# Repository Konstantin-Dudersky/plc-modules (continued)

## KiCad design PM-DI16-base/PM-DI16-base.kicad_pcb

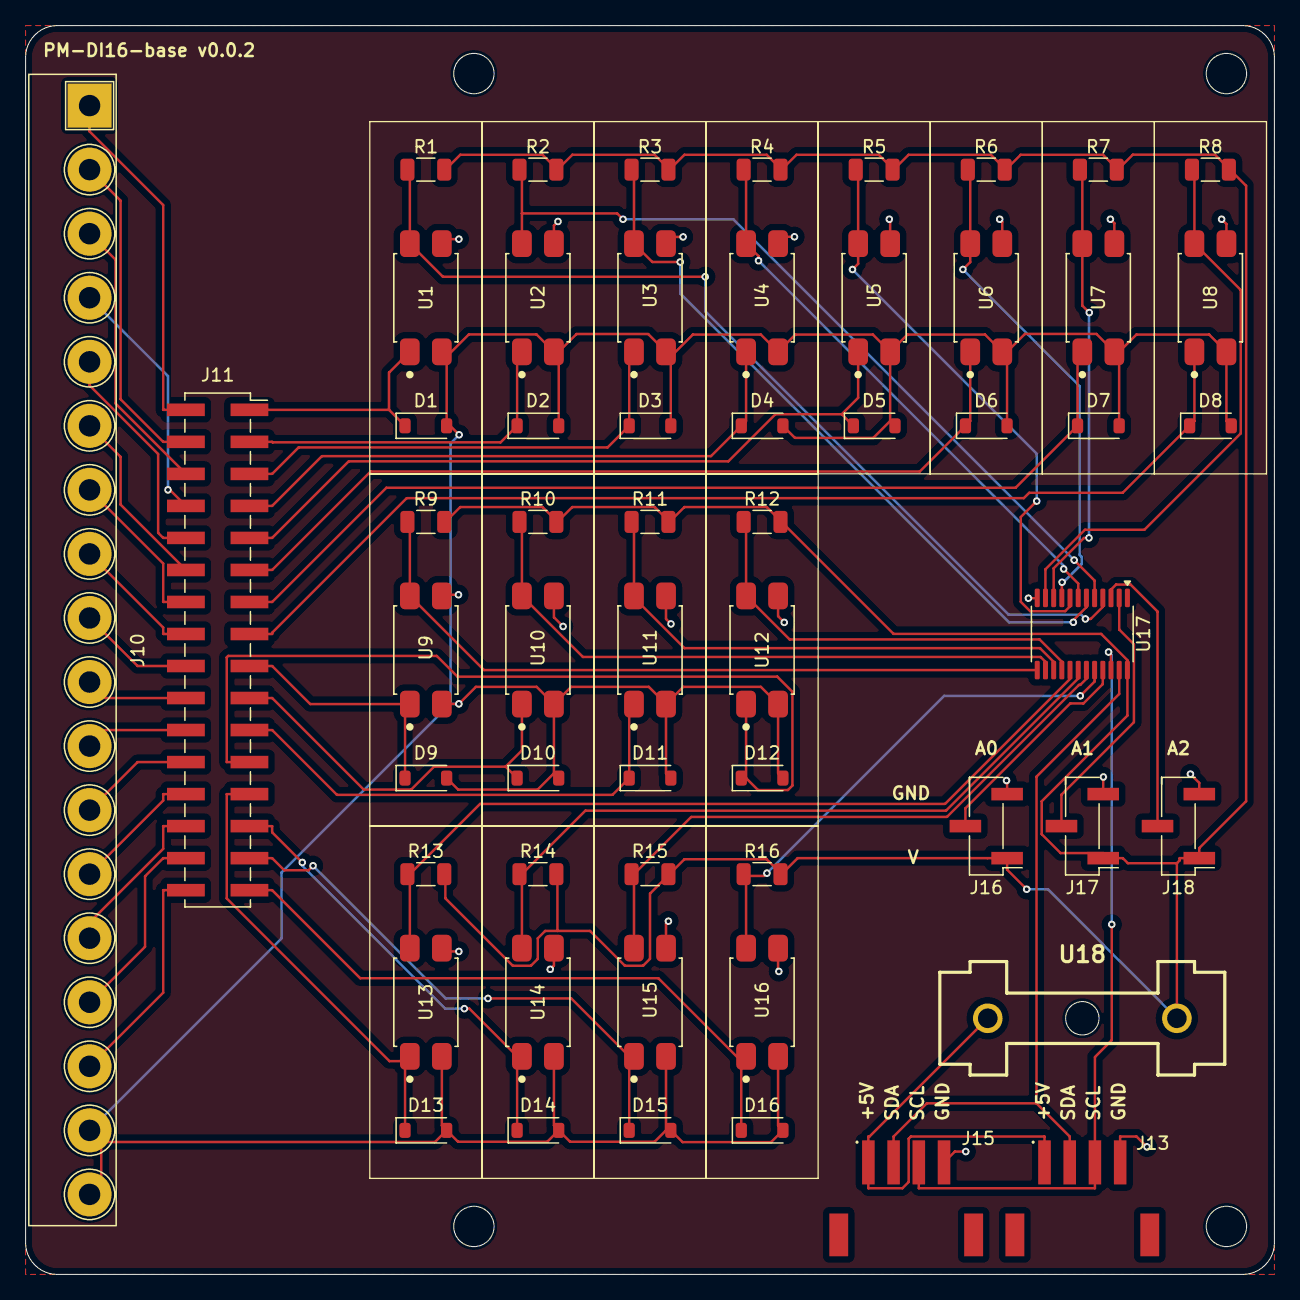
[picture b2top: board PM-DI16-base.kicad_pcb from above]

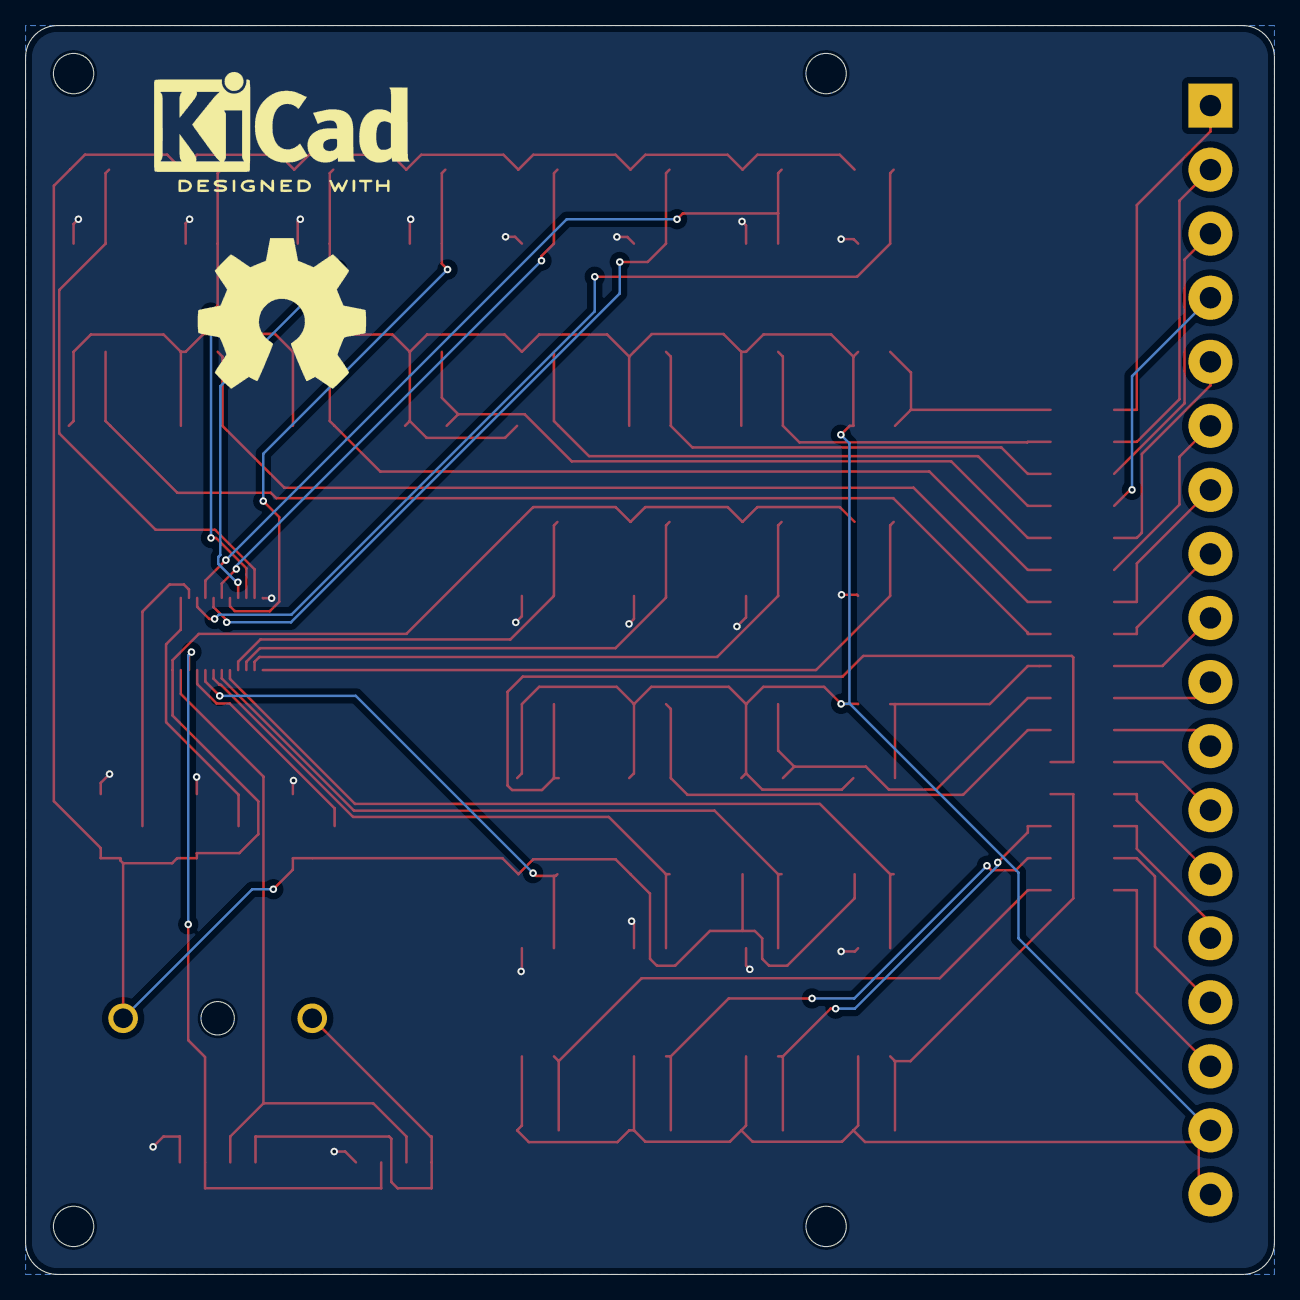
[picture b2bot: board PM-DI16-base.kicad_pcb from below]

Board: 2 copper layers, 99.1 x 99.1 mm, 63 parts (2 on the bottom side), 57 nets.

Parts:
D1, D2, D3, D4, D5, D6, D7, D8, D9, D10, D11, D12, D13, D14, D15, D16: 1N4148W; D_SOD-123
H1, H2, H3, H4: MountingHole; MountingHole_3.2mm_M3
J10: 2EDGR-5.08-18P; Degson_2EDGR-5.08-18P
J11: Conn_02x16_socket
J13, J15: S4B-PH-SM4-TB; JST_S4B-PH-SM4-TB_JST_S4B-PH-SM4-TB
J16, J17, J18: Conn_01x03; PinHeader_1x03_P2.54mm_Vertical_SMD_Pin1Left
R1, R2, R3, R4, R5, R6, R7, R8, R9, R10, R11, R12, R13, R14, R15, R16: 10k 0.25W; R_1206_3216Metric
U1, U2, U3, U4, U5, U6, U7, U8, U9, U10, U11, U12, U13, U14, U15, U16: PC817; PC817XI_SOIC254P975X460-4N
U17: PCA9555PW; TSSOP-24_4.4x7.8mm_P0.65mm
U18: 64900001039; Fuseholder
logo_kicad: KiCad-Logo2_8mm_SilkScreen
logo_oshw: OSHW-Symbol_13.4x12mm_SilkScreen

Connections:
/A0: J16.2, U17.21 (A0)
/A1: J17.2, U17.2 (A1)
/A2: J18.2, U17.3 (A2)
/M: D1.2 (A), D2.2 (A), D3.2 (A), D4.2 (A), D5.2 (A), D6.2 (A), D7.2 (A), D8.2 (A), D9.2 (A), D10.2 (A), D11.2 (A), D12.2 (A), D13.2 (A), D14.2 (A), D15.2 (A), D16.2 (A), J10.17, J10.18, U1.2, U2.2, U3.2, U4.2, U5.2, U6.2, U7.2, U8.2, U9.2, U10.2, U11.2, U12.2, U13.2, U14.2, U15.2, U16.2
/SCL: J13.3, J15.3, U17.22 (SCL)
/SDA: J13.2, J15.2, U17.23 (SDA)
GND: J13.4, J15.4, J16.3, J17.3, J18.3, U1.3, U2.3, U3.3, U4.3, U5.3, U6.3, U7.3, U8.3, U9.3, U10.3, U11.3, U12.3, U13.3, U14.3, U15.3, U16.3, U17.12 (VSS)
unnamed: D1.1 (K), J11.1, U1.1
unnamed: D2.1 (K), J11.3, U2.1
unnamed: D3.1 (K), J11.5, U3.1
unnamed: D4.1 (K), J11.7, U4.1
unnamed: D5.1 (K), J11.9, U5.1
unnamed: D6.1 (K), J11.11, U6.1
unnamed: D7.1 (K), J11.13, U7.1
unnamed: D8.1 (K), J11.15, U8.1
unnamed: D9.1 (K), J11.17, U9.1
unnamed: D10.1 (K), J11.19, U10.1
unnamed: D11.1 (K), J11.21, U11.1
unnamed: D12.1 (K), J11.23, U12.1
unnamed: D13.1 (K), J11.25, U13.1
unnamed: D14.1 (K), J11.27, U14.1
unnamed: D15.1 (K), J11.29, U15.1
unnamed: D16.1 (K), J11.31, U16.1
unnamed: J10.1, J11.2
unnamed: J10.2, J11.4
unnamed: J10.3, J11.6
unnamed: J10.4, J11.8
unnamed: J10.5, J11.10
unnamed: J10.6, J11.12
unnamed: J10.7, J11.14
unnamed: J10.8, J11.16
unnamed: J10.9, J11.18
unnamed: J10.10, J11.20
unnamed: J10.11, J11.22
unnamed: J10.12, J11.24
unnamed: J10.13, J11.26
unnamed: J10.14, J11.28
unnamed: J10.15, J11.30
unnamed: J10.16, J11.32
unnamed: J13.1, J15.1, U18.2
unnamed: R1.1, U1.4, U17.4 (IO0_0)
unnamed: R2.1, U2.4, U17.5 (IO0_1)
unnamed: R3.1, U3.4, U17.6 (IO0_2)
unnamed: R4.1, U4.4, U17.7 (IO0_3)
unnamed: R5.1, U5.4, U17.8 (IO0_4)
unnamed: R6.1, U6.4, U17.9 (IO0_5)
unnamed: R7.1, U7.4, U17.10 (IO0_6)
unnamed: R8.1, U8.4, U17.11 (IO0_7)
unnamed: R9.1, U9.4, U17.13 (IO1_0)
unnamed: R10.1, U10.4, U17.14 (IO1_1)
unnamed: R11.1, U11.4, U17.15 (IO1_2)
unnamed: R12.1, U12.4, U17.16 (IO1_3)
unnamed: R13.1, U13.4, U17.17 (IO1_4)
unnamed: R14.1, U14.4, U17.18 (IO1_5)
unnamed: R15.1, U15.4, U17.19 (IO1_6)
unnamed: R16.1, U16.4, U17.20 (IO1_7)
VDD: J16.1, J17.1, J18.1, R1.2, R2.2, R3.2, R4.2, R5.2, R6.2, R7.2, R8.2, R9.2, R10.2, R11.2, R12.2, R13.2, R14.2, R15.2, R16.2, U17.24 (VDD), U18.1

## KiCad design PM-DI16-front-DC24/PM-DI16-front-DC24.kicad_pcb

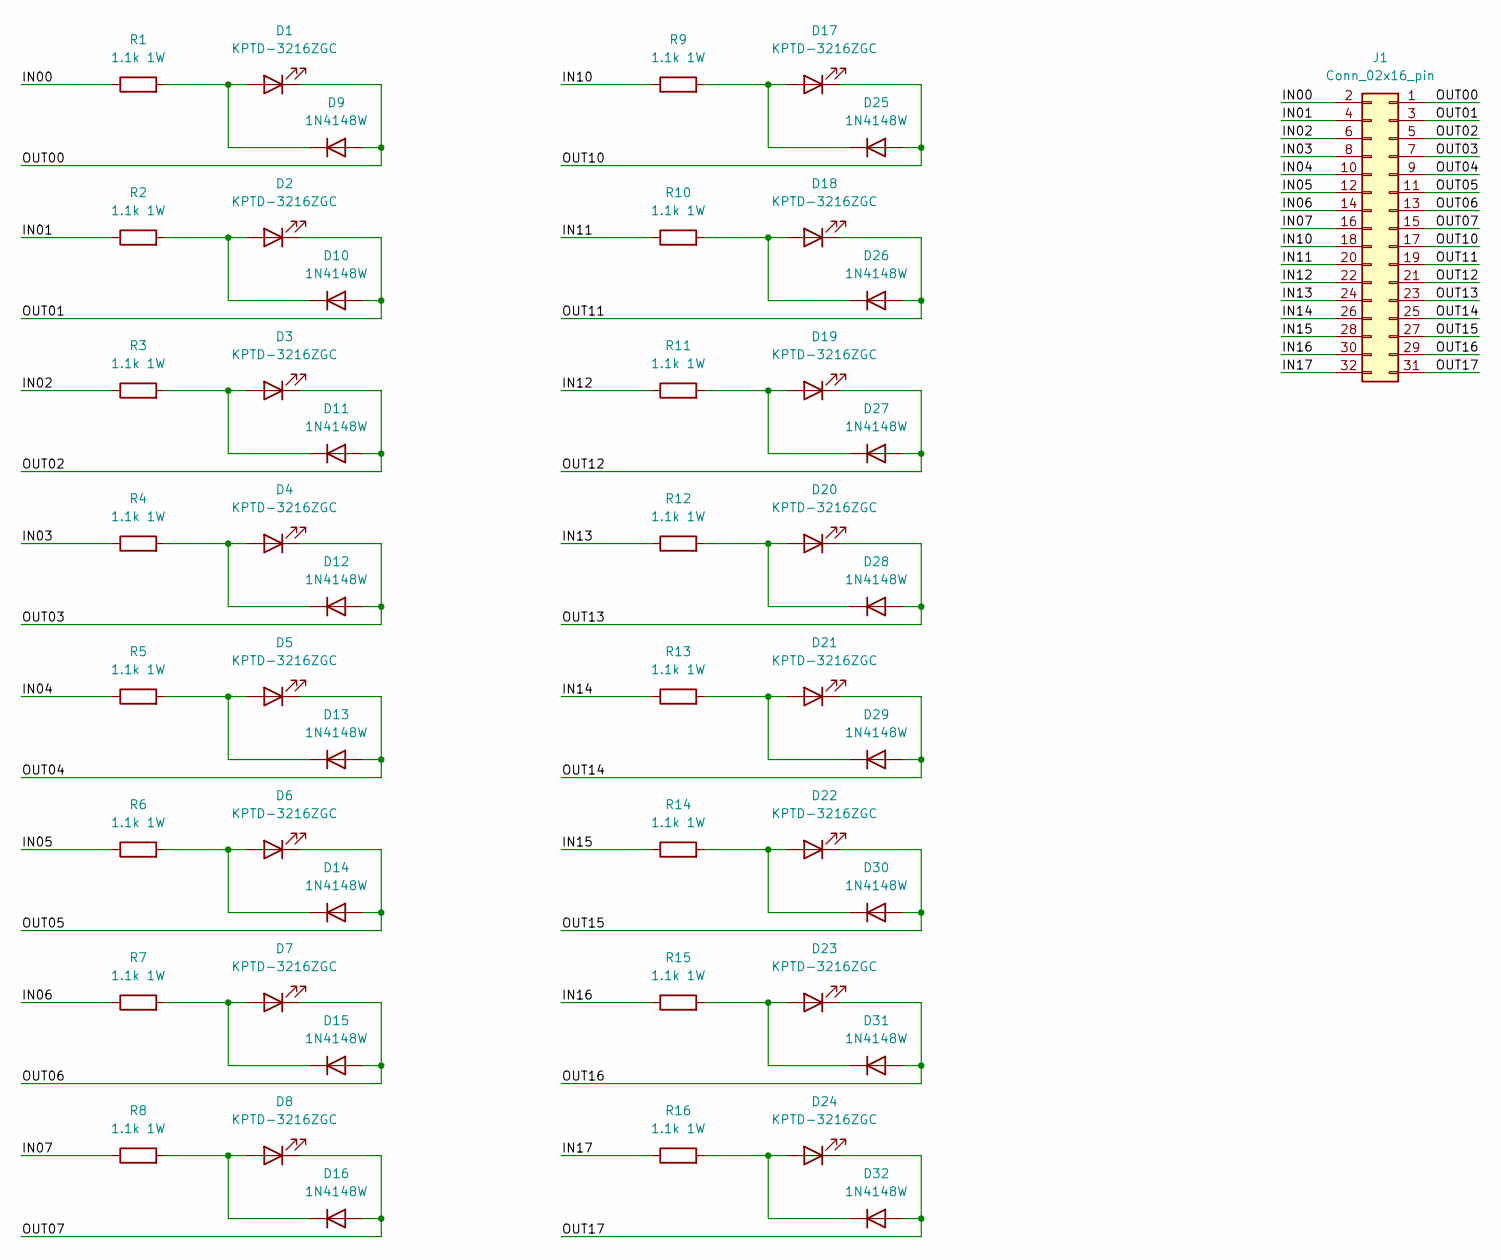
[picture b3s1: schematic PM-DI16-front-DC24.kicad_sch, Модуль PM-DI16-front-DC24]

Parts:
D1, D2, D3, D4, D5, D6, D7, D8, D17, D18, D19, D20, D21, D22, D23, D24: KPTD-3216ZGC; LED_KPTD-3216ZGC
D9, D10, D11, D12, D13, D14, D15, D16, D25, D26, D27, D28, D29, D30, D31, D32: 1N4148W; D_SOD-123; MfrPart 1N4148W
J1: Conn_02x16_pin
R1, R2, R3, R4, R5, R6, R7, R8, R9, R10, R11, R12, R13, R14, R15, R16: 1.1k 1W; R_2512_6332Metric_Pad1.40x3.35mm_HandSolder; MfgPart FRC2512F1101TS

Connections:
/IN00: J1.2, R1.1
/IN01: J1.4, R2.1
/IN02: J1.6, R3.1
/IN03: J1.8, R4.1
/IN04: J1.10, R5.1
/IN05: J1.12, R6.1
/IN06: J1.14, R7.1
/IN07: J1.16, R8.1
/IN10: J1.18, R9.1
/IN11: J1.20, R10.1
/IN12: J1.22, R11.1
/IN13: J1.24, R12.1
/IN14: J1.26, R13.1
/IN15: J1.28, R14.1
/IN16: J1.30, R15.1
/IN17: J1.32, R16.1
/OUT00: D1.1 (K), D9.2 (A), J1.1
/OUT01: D2.1 (K), D10.2 (A), J1.3
/OUT02: D3.1 (K), D11.2 (A), J1.5
/OUT03: D4.1 (K), D12.2 (A), J1.7
/OUT04: D5.1 (K), D13.2 (A), J1.9
/OUT05: D6.1 (K), D14.2 (A), J1.11
/OUT06: D7.1 (K), D15.2 (A), J1.13
/OUT07: D8.1 (K), D16.2 (A), J1.15
/OUT10: D17.1 (K), D25.2 (A), J1.17
/OUT11: D18.1 (K), D26.2 (A), J1.19
/OUT12: D19.1 (K), D27.2 (A), J1.21
/OUT13: D20.1 (K), D28.2 (A), J1.23
/OUT14: D21.1 (K), D29.2 (A), J1.25
/OUT15: D22.1 (K), D30.2 (A), J1.27
/OUT16: D23.1 (K), D31.2 (A), J1.29
/OUT17: D24.1 (K), D32.2 (A), J1.31
unnamed: D1.2 (A), D9.1 (K), R1.2
unnamed: D2.2 (A), D10.1 (K), R2.2
unnamed: D3.2 (A), D11.1 (K), R3.2
unnamed: D4.2 (A), D12.1 (K), R4.2
unnamed: D5.2 (A), D13.1 (K), R5.2
unnamed: D6.2 (A), D14.1 (K), R6.2
unnamed: D7.2 (A), D15.1 (K), R7.2
unnamed: D8.2 (A), D16.1 (K), R8.2
unnamed: D17.2 (A), D25.1 (K), R9.2
unnamed: D18.2 (A), D26.1 (K), R10.2
unnamed: D19.2 (A), D27.1 (K), R11.2
unnamed: D20.2 (A), D28.1 (K), R12.2
unnamed: D21.2 (A), D29.1 (K), R13.2
unnamed: D22.2 (A), D30.1 (K), R14.2
unnamed: D23.2 (A), D31.1 (K), R15.2
unnamed: D24.2 (A), D32.1 (K), R16.2

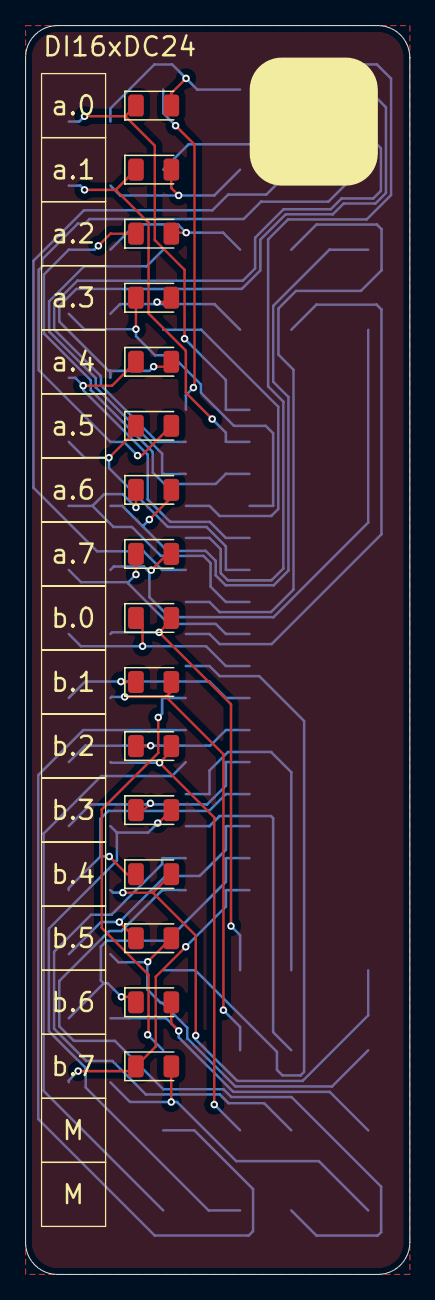
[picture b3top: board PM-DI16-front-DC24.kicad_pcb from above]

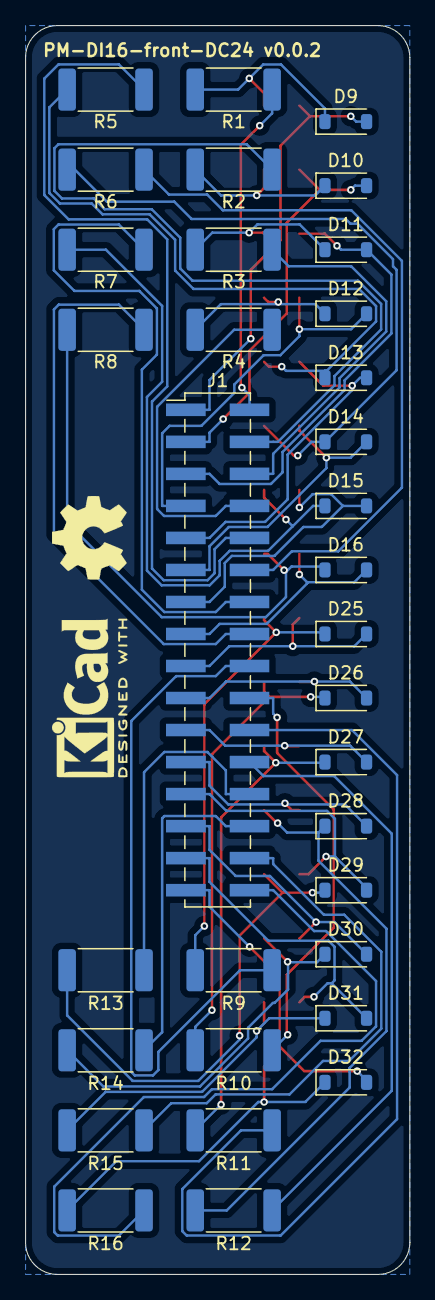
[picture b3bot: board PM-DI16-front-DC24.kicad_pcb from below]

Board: 2 copper layers, 30.5 x 99.1 mm, 50 parts (34 on the bottom side), 48 nets.

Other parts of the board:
Logo_kicad: KiCad-Logo2_5mm_SilkScreen

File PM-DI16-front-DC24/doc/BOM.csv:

"Reference","Value","Qty","NextPCB_price","NextPCB_url","Datasheet"
"D1,D2,D3,D4,D5,D6,D7,D8,D17,D18,D19,D20,D21,D22,D23,D24","KPTD-3216ZGC ","16","0.39735","https://www.hqonline.com/product-detail/kingbright-kptd-3216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","https://www.kingbright.com/content/listitem/psearch/170"
"D9,D10,D11,D12,D13,D14,D15,D16,D25,D26,D27,D28,D29,D30,D31,D32","1N4148W","16","0.00811","https://www.hqonline.com/product-detail/switching-diodes--sm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","~"
"J1,J2","Conn_02x08_Odd_Even","2","0.27407","https://www.hqonline.com/product-detail/pin-headers-hctl-pz2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","~"
"R1,R2,R3,R4,R5,R6,R7,R8,R9,R10,R11,R12,R13,R14,R15,R16","1.1k 1W","16","0.01655","https://www.hqonline.com/product-detail/chip-resistors-fojan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","https://www.hqonline.com/product-detail/chip-resistors-fojan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"

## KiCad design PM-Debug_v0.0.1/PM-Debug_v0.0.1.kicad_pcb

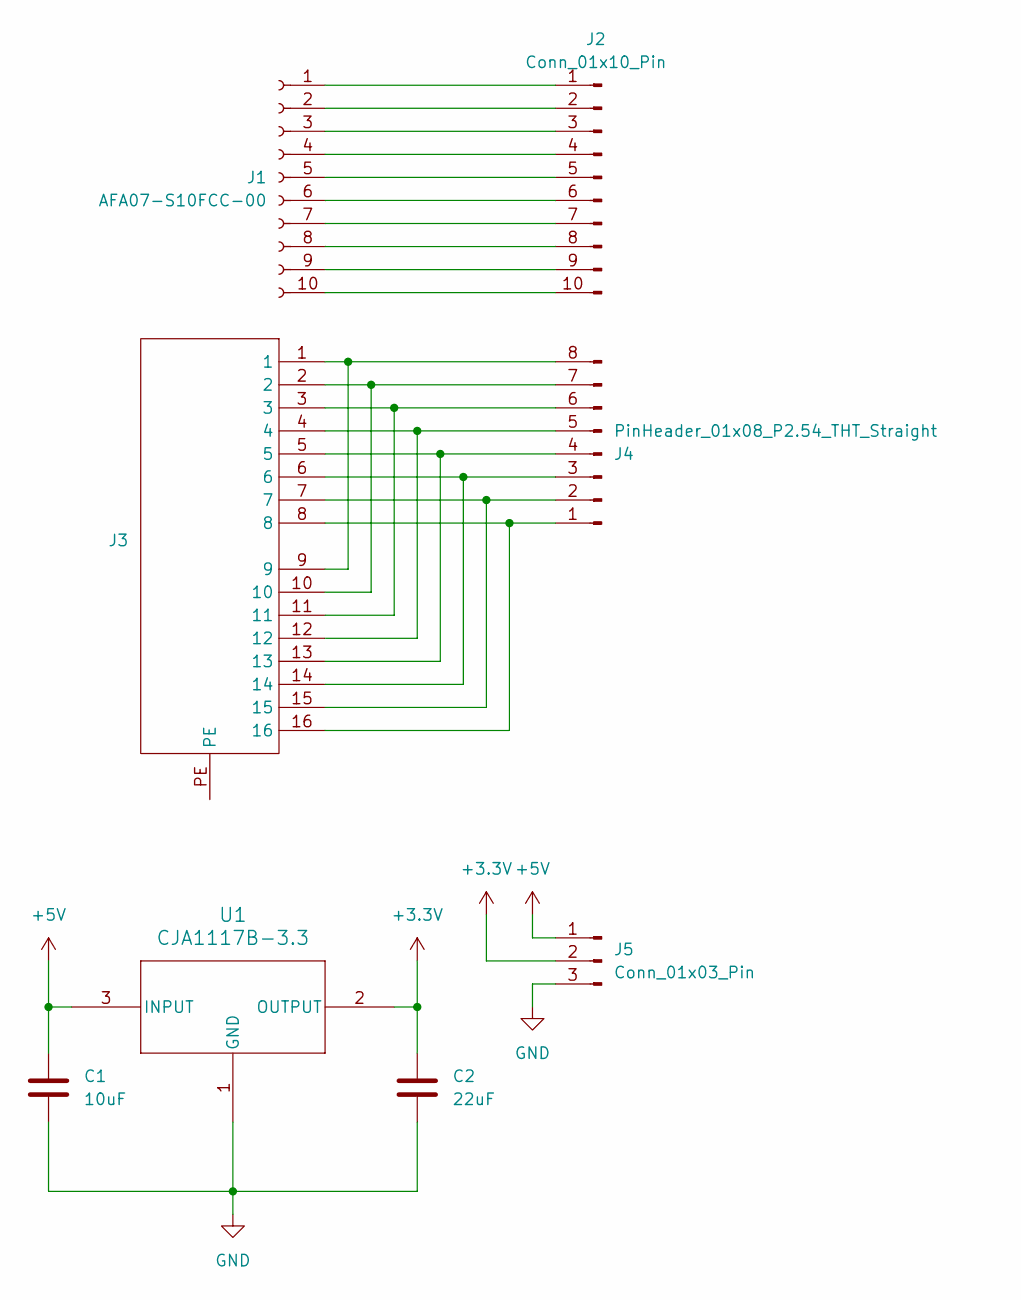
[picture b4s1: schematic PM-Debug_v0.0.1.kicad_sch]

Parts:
C1: 10uF; C_1206_3216Metric_Pad1.33x1.80mm_HandSolder; part_ipn C_10uF_16V_1206
C2: 22uF; C_1206_3216Metric_Pad1.33x1.80mm_HandSolder; part_ipn C_22uF_16V_1206
J1: AFA07-S10FCC-00; CONN10_AFA07-S10_JUS
J2: Conn_01x10_Pin; PinHeader_1x10_P2.54mm_Vertical
J3: HC-WK88-H16-1X2-DB
J4: PinHeader_01x08_P2.54_THT_Straight; PinHeader_1x08_P2.54mm_Vertical; part_ipn PinHeader_01x08_P2.54_THT_Straight
J5: Conn_01x03_Pin; PinHeader_1x03_P2.54mm_Vertical
U1: CJA1117B-3.3; SOT-89-3; part_ipn CJA1117B-3.3

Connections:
+3.3V: C2.1, J5.2, U1.2 (OUTPUT)
+5V: C1.1, J5.1, U1.3 (INPUT)
GND: C1.2, C2.2, J5.3, U1.1 (GND)
unnamed: J1.1, J2.1
unnamed: J1.2, J2.2
unnamed: J1.3, J2.3
unnamed: J1.4, J2.4
unnamed: J1.5, J2.5
unnamed: J1.6, J2.6
unnamed: J1.7, J2.7
unnamed: J1.8, J2.8
unnamed: J1.9, J2.9
unnamed: J1.10, J2.10
unnamed: J3.8, J3.16, J4.1
unnamed: J3.7, J3.15, J4.2
unnamed: J3.6, J3.14, J4.3
unnamed: J3.5, J3.13, J4.4
unnamed: J3.4, J3.12, J4.5
unnamed: J3.3, J3.11, J4.6
unnamed: J3.2, J3.10, J4.7
unnamed: J3.1, J3.9, J4.8

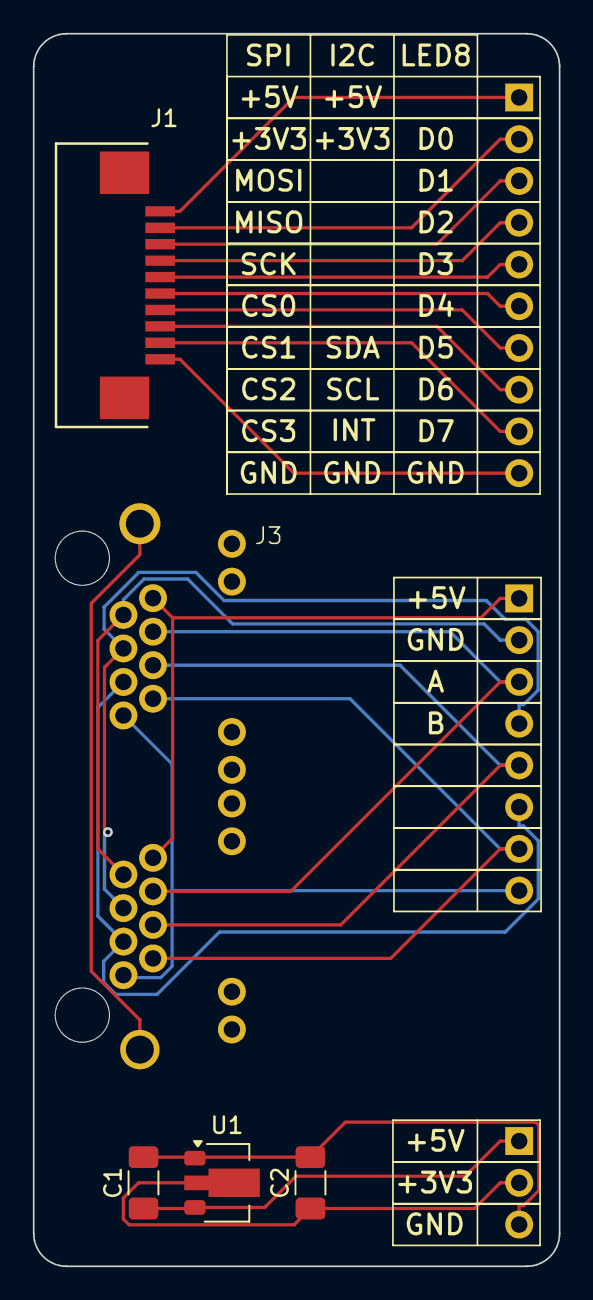
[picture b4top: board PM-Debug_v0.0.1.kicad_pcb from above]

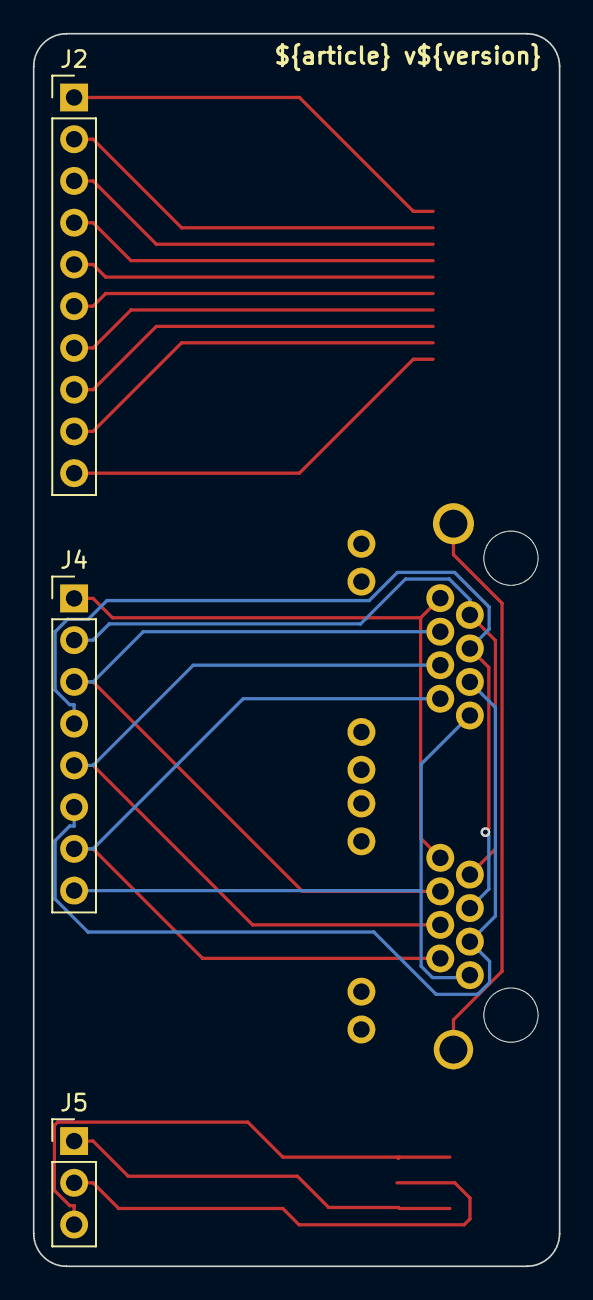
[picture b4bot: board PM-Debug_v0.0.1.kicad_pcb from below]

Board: 2 copper layers, 32.0 x 75.0 mm, 8 parts (3 on the bottom side), 21 nets.

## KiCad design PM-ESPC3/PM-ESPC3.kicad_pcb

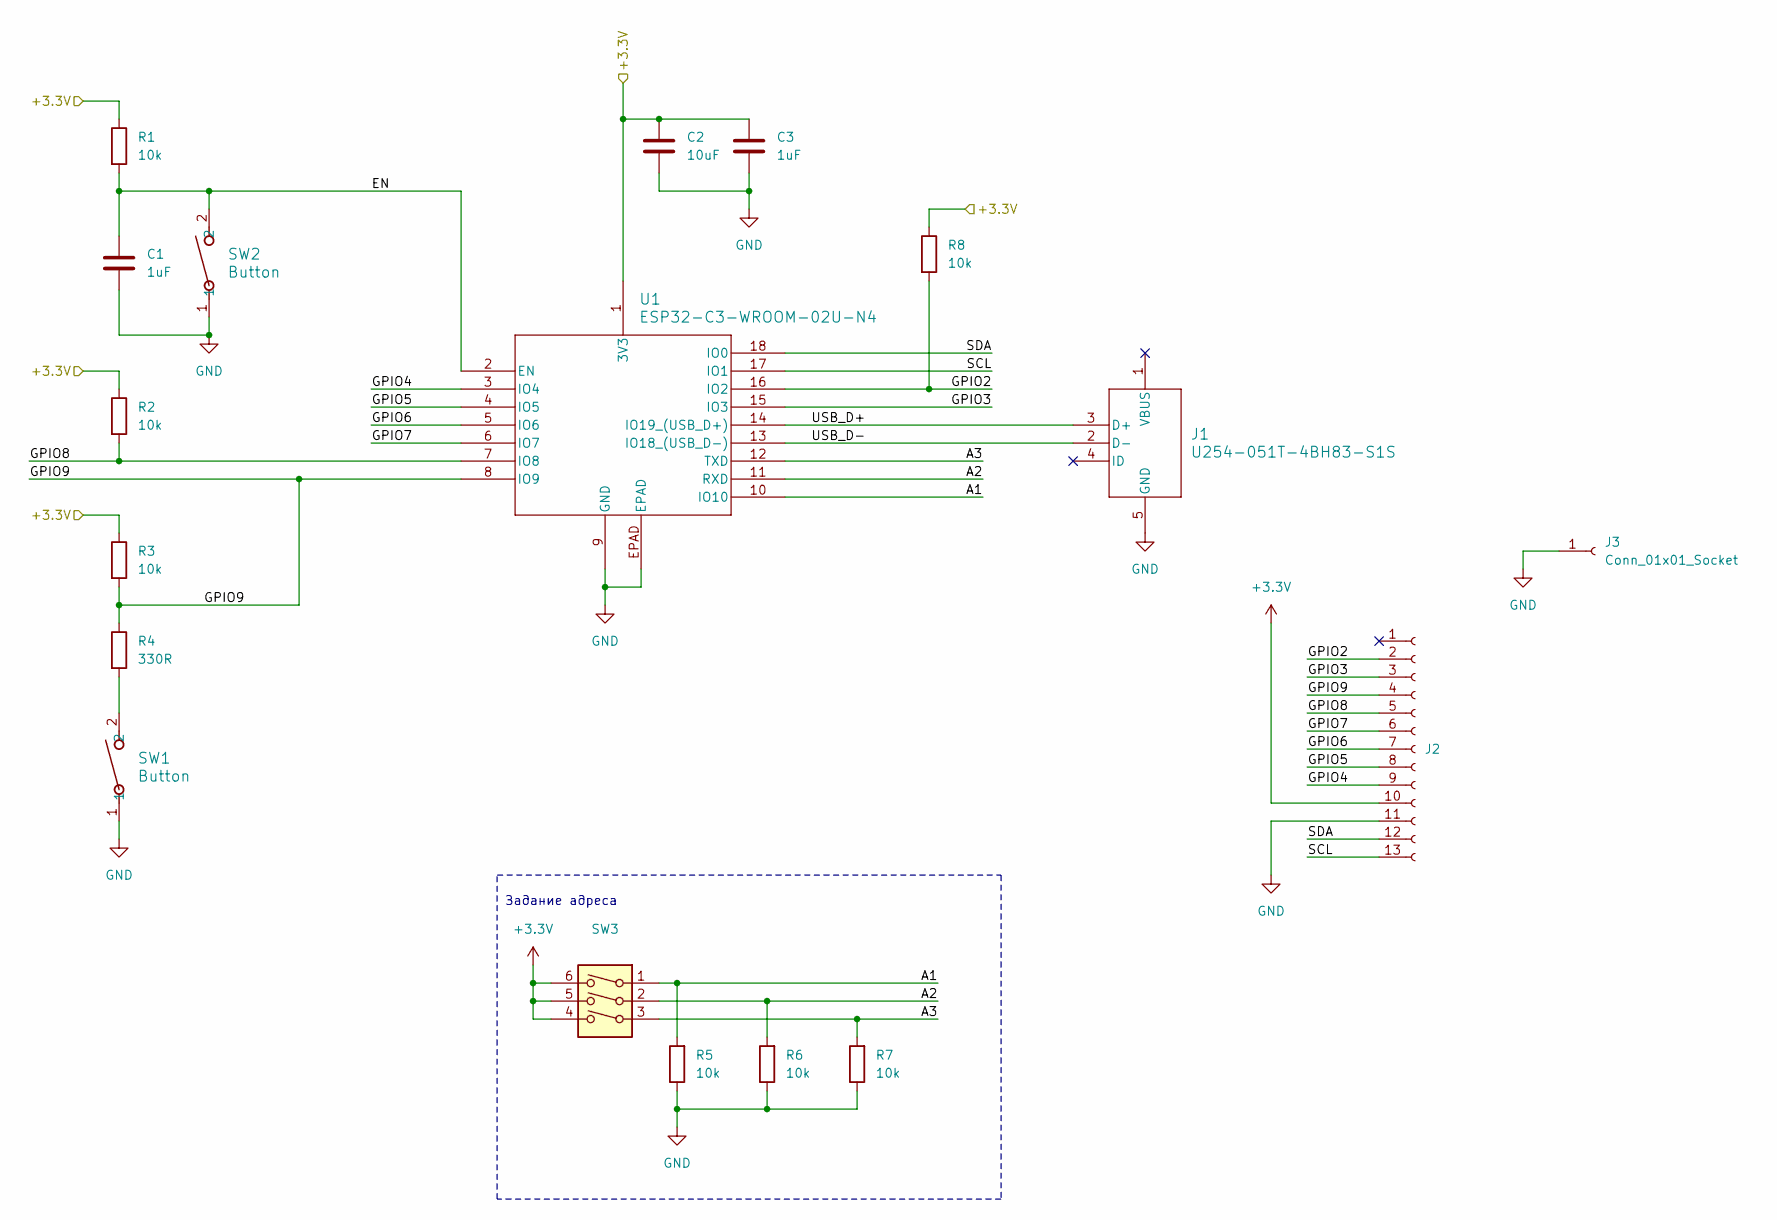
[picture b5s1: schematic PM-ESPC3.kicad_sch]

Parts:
C1: 1uF; C_1206_3216Metric_Pad1.33x1.80mm_HandSolder; part_ipn C_1uF_50V_1206
C2: 10uF; C_1206_3216Metric_Pad1.33x1.80mm_HandSolder; part_ipn C_10uF_16V_1206
C3: 1uF; C_1206_3216Metric_Pad1.33x1.80mm_HandSolder; part_ipn C_1uF_16V_1206
J1: U254-051T-4BH83-S1S; CONN5_H83-S1S_XKB; part_ipn U254-051T-4BH83-S1S
J2: Conn_01x13_Socket; PinHeader_1x13_P2.54mm_Vertical
J3: Conn_01x01_Socket; PinHeader_1x01_P2.54mm_Vertical
R1, R2, R3, R5, R6, R7, R8: 10k; R_1206_3216Metric_Pad1.30x1.75mm_HandSolder; part_ipn R_10k_1206_1%
R4: 330R; R_1206_3216Metric_Pad1.30x1.75mm_HandSolder; part_ipn R_330R_1206_1%
SW1, SW2: Button; SW_TS-1088_XNP-M; part_ipn TS-1088-AR02016
SW3: DIP_SW-3P-P2.54-THT-Top; SW_DIP_SPSTx03_Slide_9.78x9.8mm_W7.62mm_P2.54mm; part_ipn DIP_SW-3P-P2.54-THT-Top
U1: ESP32-C3-WROOM-02U-N4; ESP32-C3-WROOM-02U_EXP

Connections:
+3.3V: C2.2, C3.1, J2.10, R1.1, R2.1, R3.1, R8.1, SW3.4, SW3.5, SW3.6, U1.1 (3V3)
/A1: R5.2, SW3.1, U1.10 (IO10)
/A2: R6.2, SW3.2, U1.11 (RXD)
/A3: R7.2, SW3.3, U1.12 (TXD)
/EN: C1.1, R1.2, SW2.2, U1.2 (EN)
/GPIO2: J2.2, R8.2, U1.16 (IO2)
/GPIO3: J2.3, U1.15 (IO3)
/GPIO4: J2.9, U1.3 (IO4)
/GPIO5: J2.8, U1.4 (IO5)
/GPIO6: J2.7, U1.5 (IO6)
/GPIO7: J2.6, U1.6 (IO7)
/GPIO8: J2.5, R2.2, U1.7 (IO8)
/GPIO9: J2.4, R3.2, R4.1, U1.8 (IO9)
/SCL: J2.13, U1.17 (IO1)
/SDA: J2.12, U1.18 (IO0)
/USB_D+: J1.3 (D+), U1.14 (IO19_(USB_D+))
/USB_D-: J1.2 (D-), U1.13 (IO18_(USB_D-))
GND: C1.2, C2.1, C3.2, J1.5 (GND), J2.11, J3.1, R5.1, R6.1, R7.1, SW1.1, SW2.1, U1.9 (GND), U1.EPAD
unnamed: R4.2, SW1.2

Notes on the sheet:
Задание адреса

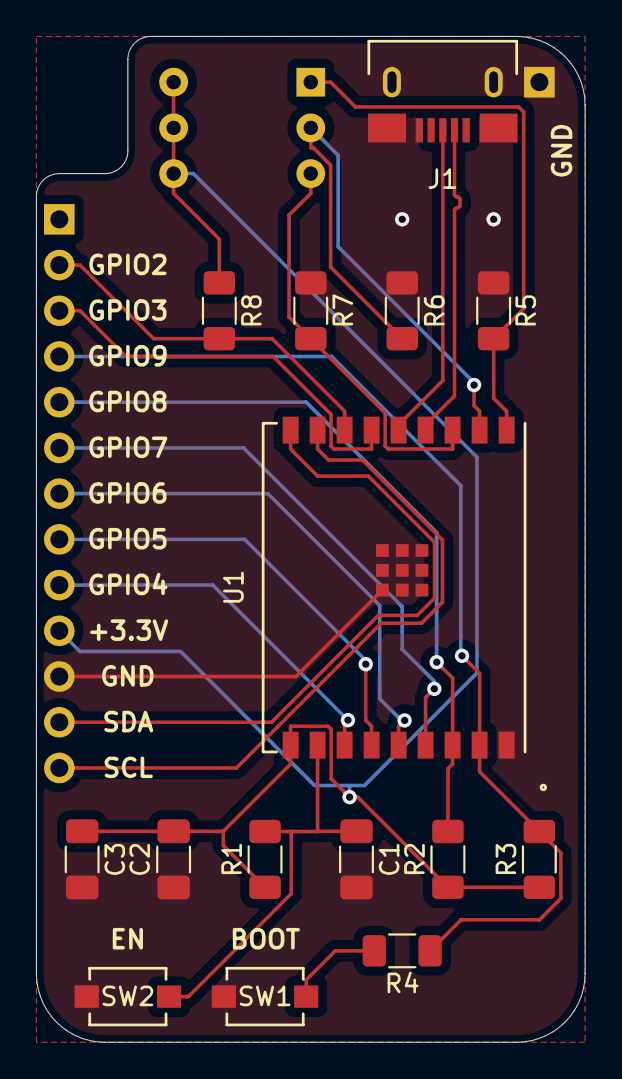
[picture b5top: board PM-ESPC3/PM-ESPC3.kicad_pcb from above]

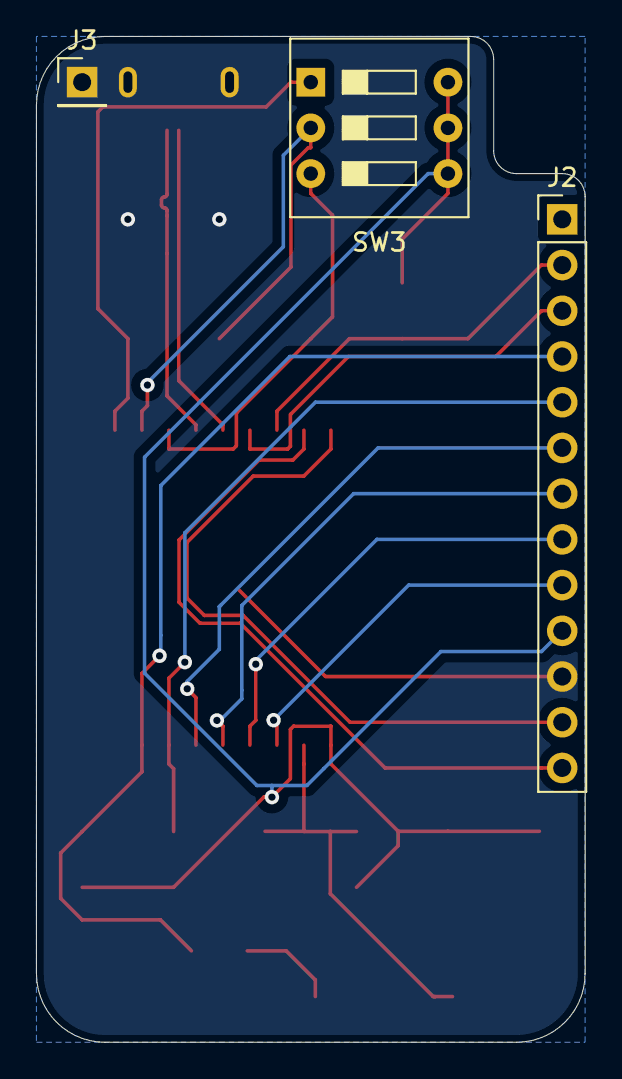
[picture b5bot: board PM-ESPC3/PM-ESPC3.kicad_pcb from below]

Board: 2 copper layers, 30.5 x 55.9 mm, 18 parts (3 on the bottom side), 19 nets.
